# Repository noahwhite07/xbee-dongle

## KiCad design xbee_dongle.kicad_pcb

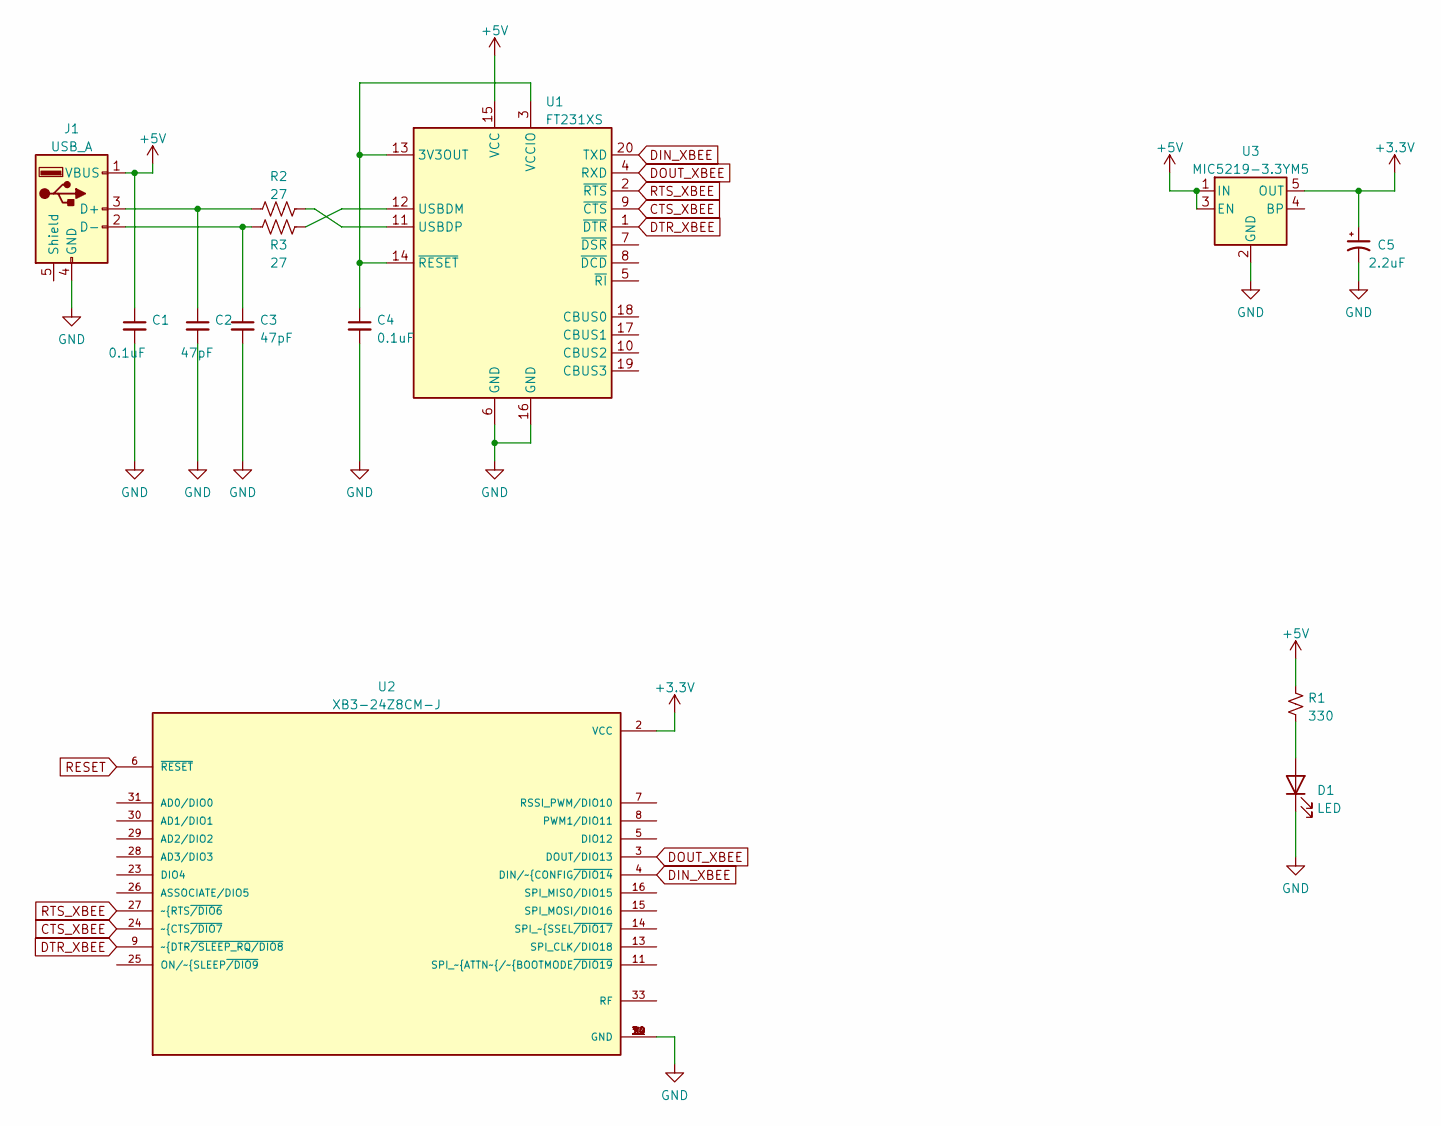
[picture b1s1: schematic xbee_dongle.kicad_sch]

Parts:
C1, C4: 0.1uF; C_0805_2012Metric_Pad1.18x1.45mm_HandSolder
C2, C3: 47pF; C_0805_2012Metric_Pad1.18x1.45mm_HandSolder
C5: 2.2uF; CP_EIA-3216-12_Kemet-S_Pad1.58x1.35mm_HandSolder
D1: LED; LED_0805_2012Metric_Pad1.15x1.40mm_HandSolder
J1: USB_A; USB_A_CNCTech_1001-011-01101_Horizontal
R1: 330; R_0805_2012Metric_Pad1.20x1.40mm_HandSolder
R2, R3: 27; R_0805_2012Metric_Pad1.20x1.40mm_HandSolder
U1: FT231XS; SSOP-20_3.9x8.7mm_P0.635mm
U2: XB3-24Z8CM-J; XB3-24Z8UM-J; PARTREV N/A
U3: MIC5219-3.3YM5; SOT-23-5

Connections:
+3.3V: C5.1, U2.2 (VCC), U3.5 (OUT)
+5V: C1.1, J1.1 (VBUS), R1.1, U1.15 (VCC), U3.1 (IN), U3.3 (EN)
CTS_XBEE: U1.9 (~CTS), U2.24 (~CTS~{/DIO7)
DIN_XBEE: U1.20 (TXD), U2.4 (DIN/~CONFIG~{/DIO14)
DOUT_XBEE: U1.4 (RXD), U2.3 (DOUT/DIO13)
DTR_XBEE: U1.1 (~DTR), U2.9 (~DTR~{/SLEEP_RQ/DIO8)
GND: C1.2, C2.2, C3.2, C4.2, C5.2, D1.1 (K), J1.4 (GND), U1.6 (GND), U1.16 (GND), U2.1 (GND), U2.10 (GND), U2.12 (GND), U2.21 (GND), U2.32 (GND), U2.34 (GND), U3.2 (GND)
unnamed: C2.1, J1.3 (D+), R2.1
unnamed: C3.1, J1.2 (D-), R3.1
unnamed: D1.2 (A), R1.2
unnamed: R3.2, U1.12 (USBDM)
unnamed: R2.2, U1.11 (USBDP)
unnamed: C4.1, U1.3 (VCCIO), U1.13 (3V3OUT), U1.14 (~RESET)
RESET: U2.6 (~RESET)
RTS_XBEE: U1.2 (~RTS), U2.27 (~RTS~{/DIO6)

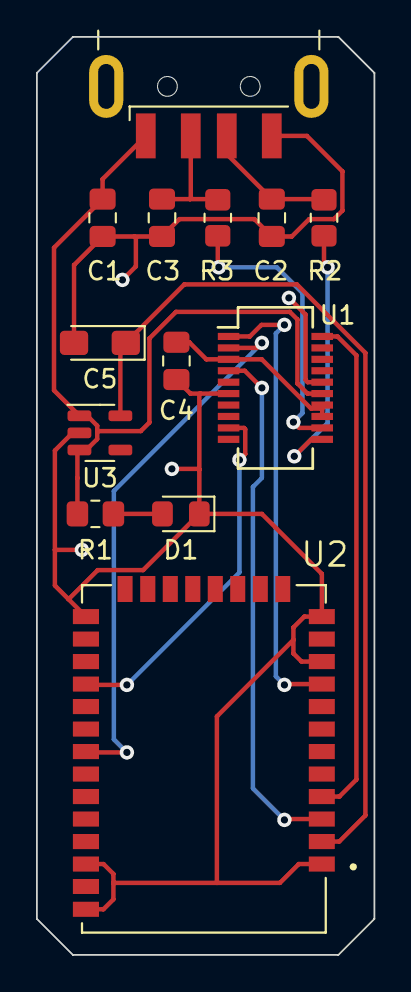
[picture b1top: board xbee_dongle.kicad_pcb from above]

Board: 2 copper layers, 18.8 x 51.0 mm, 13 parts (0 on the bottom side), 14 nets.
